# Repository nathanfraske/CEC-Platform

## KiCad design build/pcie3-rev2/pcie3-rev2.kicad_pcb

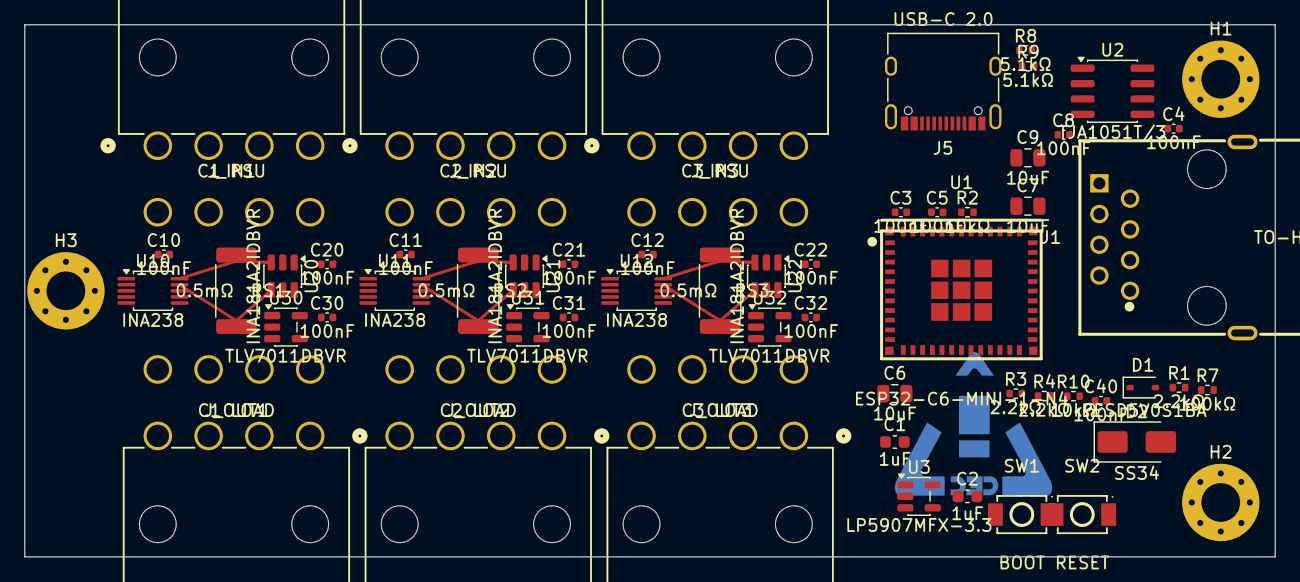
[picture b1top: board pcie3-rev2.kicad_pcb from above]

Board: 4 copper layers, 103.4 x 44.0 mm, 58 parts (1 on the bottom side), 32 nets.

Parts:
C1, C2: 1uF; C_0603_1608Metric
C3, C4, C5, C8, C10, C11, C12, C20, C21, C22, C30, C31, C32, C40: 100nF; C_0402_1005Metric
C6, C7, C9: 10uF; C_0805_2012Metric
D1: PESD5V0S1BA; D_SOD-323
D2: SS34; D_SMA
H1, H2, H3: MountingHole_3.2mm_M3_Pad_Via
J1: TO-HUB; RJ45_FTP_Shielded_Horizontal
J5: USB-C 2.0; USB_C_Receptacle_XKB_U262-16XN-4BVC11
J_IN1: C1 PSU; Molex_Mini-Fit_Jr_45586_2x04_P4.20mm_Horizontal
J_IN2: C2 PSU; Molex_Mini-Fit_Jr_45586_2x04_P4.20mm_Horizontal
J_IN3: C3 PSU; Molex_Mini-Fit_Jr_45586_2x04_P4.20mm_Horizontal
J_OUT1: C1 LOAD; Molex_Mini-Fit_Jr_45586_2x04_P4.20mm_Horizontal
J_OUT2: C2 LOAD; Molex_Mini-Fit_Jr_45586_2x04_P4.20mm_Horizontal
J_OUT3: C3 LOAD; Molex_Mini-Fit_Jr_45586_2x04_P4.20mm_Horizontal
LOGO1: CEC_Logo_Copper
R1, R3, R4: 2.2kΩ; R_0402_1005Metric
R2, R10: 10kΩ; R_0402_1005Metric
R7: 100kΩ; R_0402_1005Metric
R8, R9: 5.1kΩ; R_0402_1005Metric
RS1, RS2, RS3: 0.5mΩ; R_2512_6332Metric
SW1: BOOT; TS-1088-AR02016
SW2: RESET; TS-1088-AR02016
U1: ESP32-C6-MINI-1-N4; ESP32-C6-MINI-1
U2: TJA1051T/3; SOIC-8_3.9x4.9mm_P1.27mm
U3: LP5907MFX-3.3; SOT-23-5
U10, U11, U12: INA238; VSSOP-10_3x3mm_P0.5mm
U20, U21, U22: INA181A2IDBVR; SOT-23-6
U30, U31, U32: TLV7011DBVR; SOT-23-5

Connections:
+3V3: C2.1, C3.1, C7.1, C8.1, C10.1, C11.1, C12.1, C20.1, C21.1, C22.1, C30.1, C31.1, C32.1, R2.1, R3.2, R4.2, U1.3, U2.5, U3.5, U10.6, U11.2, U11.6, U12.1, U12.6, U20.6, U21.6, U22.6, U30.5, U31.5, U32.5
+5VSB: C1.1, C4.1, C6.1, D2.1, J1.1, U2.3, U3.1, U3.3
/CAN_H: J1.3, U2.7
/CAN_L: J1.6, U2.6
/CAN_RX: U1.27, U2.4
/CAN_TX: U1.26, U2.1
/DETAMPC1: U20.1, U30.3
/DETAMPC2: U21.1, U31.3
/DETAMPC3: U22.1, U32.3
/DETC1: U1.28, U30.1
/DETC2: U1.29, U31.1
/DETC3: U1.16, U32.1
/DETECT: D1.1, J1.8, R1.1, R7.1
/DETECT_SENSE: R7.2, U1.12
/EN: C5.1, R2.2, SW2.2, U1.8
/GPIO0: SW1.2, U1.23
/I2C_SCL: R4.1, U1.25, U10.5, U11.5, U12.5
/I2C_SDA: R3.1, U1.24, U10.4, U11.4, U12.4
/SENSEC1_HI: J_IN1.1, J_IN1.2, J_IN1.3, RS1.1, U10.10, U20.3
/SENSEC1_LO: J_OUT1.1, J_OUT1.2, J_OUT1.3, RS1.2, U10.8, U10.9, U20.4
/SENSEC2_HI: J_IN2.1, J_IN2.2, J_IN2.3, RS2.1, U11.10, U21.3
/SENSEC2_LO: J_OUT2.1, J_OUT2.2, J_OUT2.3, RS2.2, U11.8, U11.9, U21.4
/SENSEC3_HI: J_IN3.1, J_IN3.2, J_IN3.3, RS3.1, U12.10, U22.3
/SENSEC3_LO: J_OUT3.1, J_OUT3.2, J_OUT3.3, RS3.2, U12.8, U12.9, U22.4
/THRESH: C40.1, R10.2, U30.4, U31.4, U32.4
/THRESH_PWM: R10.1, U1.19
/USB_CC1: J5.A5, R8.1
/USB_CC2: J5.B5, R9.1
/USB_DM: J5.A7, J5.B7, U1.17
/USB_DP: J5.A6, J5.B6, U1.18
/VBUS: C9.1, D2.2, J5.A4, J5.A9, J5.B4, J5.B9
GND: C1.2, C2.2, C3.2, C4.2, C5.2, C6.2, C7.2, C8.2, C9.2, C10.2, C11.2, C12.2, C20.2, C21.2, C22.2, C30.2, C31.2, C32.2, C40.2, D1.2, H1.1, H2.1, H3.1, J1.2, J1.SH1, J1.SH2, J5.A1, J5.A12, J5.B1, J5.B12, J5.S1, J_IN1.4, J_IN1.5, J_IN1.6, J_IN1.7, J_IN1.8, J_IN2.4, J_IN2.5, J_IN2.6, J_IN2.7, J_IN2.8, J_IN3.4, J_IN3.5, J_IN3.6, J_IN3.7, J_IN3.8, J_OUT1.4, J_OUT1.5, J_OUT1.6, J_OUT1.7, J_OUT1.8, J_OUT2.4, J_OUT2.5, J_OUT2.6, J_OUT2.7, J_OUT2.8, J_OUT3.4, J_OUT3.5, J_OUT3.6, J_OUT3.7, J_OUT3.8, R1.2, R8.2, R9.2, SW1.1, SW2.1, U1.1, U1.2, U1.11, U1.14, U1.36, U1.37, U1.38, U1.39, U1.40, U1.41, U1.42, U1.43, U1.44, U1.45, U1.46, U1.47, U1.48, U1.49, U1.50, U1.51, U1.52, U1.53, U2.2, U2.8, U3.2, U10.1, U10.2, U10.7, U11.1, U11.7, U12.2, U12.7, U20.2, U20.5, U21.2, U21.5, U22.2, U22.5, U30.2, U31.2, U32.2

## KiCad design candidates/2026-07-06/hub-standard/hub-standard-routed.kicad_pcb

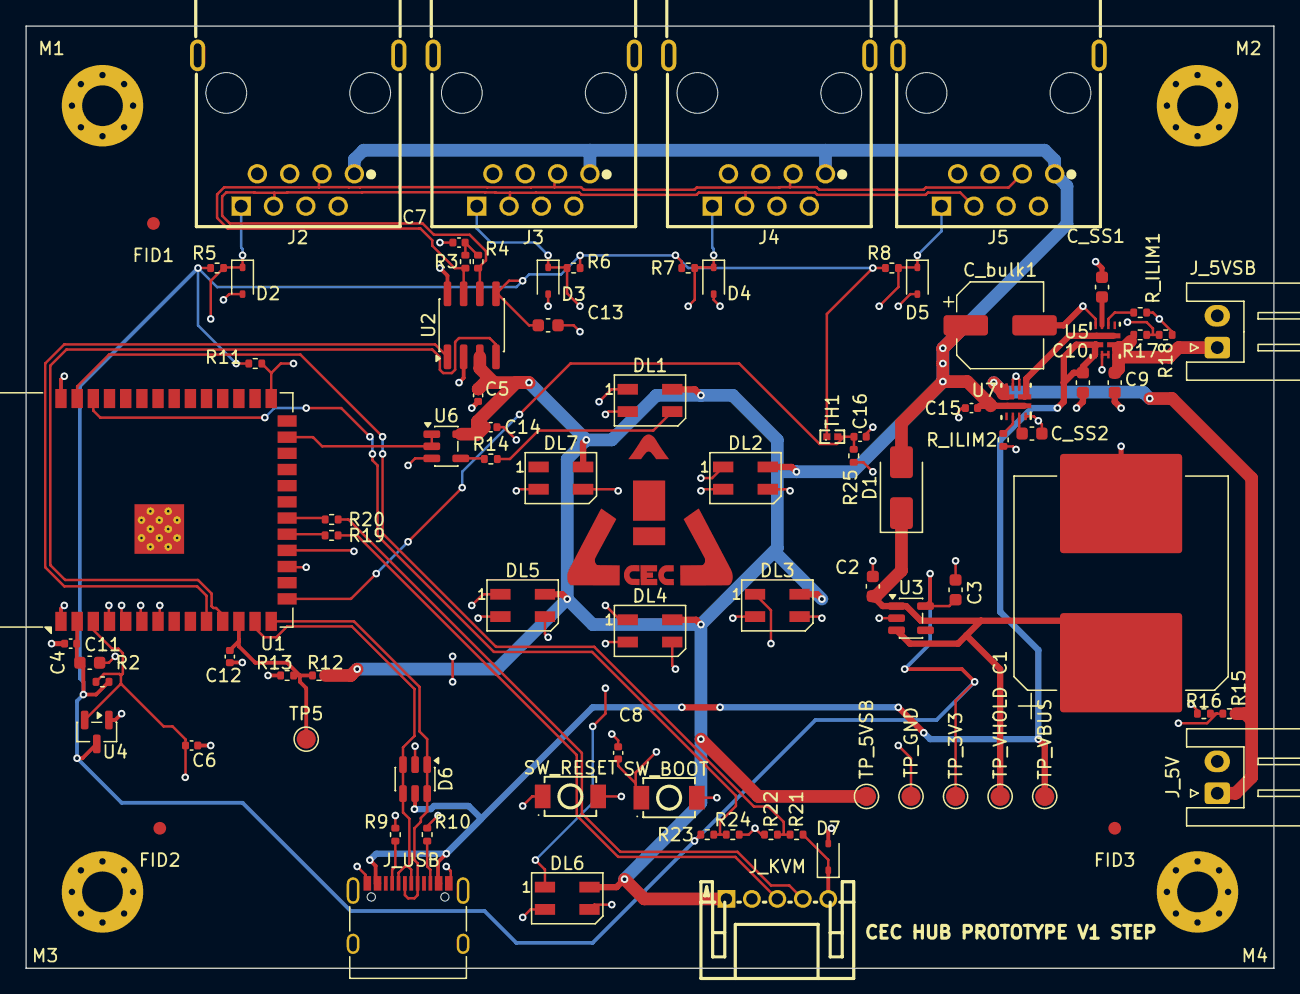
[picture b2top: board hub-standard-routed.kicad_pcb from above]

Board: 4 copper layers, 98.0 x 74.0 mm, 91 parts (0 on the bottom side), 47 nets.

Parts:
C1: 4700uF; CP_Elec_16x17.5
C2, C3, C9, C10: 1uF; C_0603_1608Metric
C4, C5, C6, C8, C14, C15, C16: 100nF; C_0402_1005Metric
C7: 4n7; C_0402_1005Metric
C11: 10uF; C_0603_1608Metric
C12: 10nF; C_0402_1005Metric
C13: 100nF; C_0603_1608Metric
C_SS1, C_SS2: 2.2uF; C_0603_1608Metric
C_bulk1: 470uF; CP_Elec_6.3x7.7
D1: SS14; D_SMA
D2, D3, D4, D5, D7: PESD5V0S1BA; D_SOD-323
D6: USBLC6-2SC6; SOT-23-6
DL1, DL2, DL3, DL4, DL5, DL6, DL7: SK6812MINI-E; LED_SK6812MINI_PLCC4_3.5x3.5mm_P1.75mm
FID1, FID2, FID3: Fiducial_1mm_Mask2mm
J2: PORT1; RJ45_FTP_Shielded_Horizontal
J3: PORT2; RJ45_FTP_Shielded_Horizontal
J4: PORT3; RJ45_FTP_Shielded_Horizontal
J5: PORT4; RJ45_FTP_Shielded_Horizontal
J_5V: MAIN_5V_IN; JST_XH_S2B-XH-A_1x02_P2.50mm_Horizontal
J_5VSB: 5VSB_IN; JST_XH_S2B-XH-A_1x02_P2.50mm_Horizontal
J_KVM: CEC_NANOKVM_AUX_5P; JST_PH_S5B-PH-K-S_1x05_P2.00mm_Horizontal
J_USB: USB-C; USB_C_Receptacle_XKB_U262-16XN-4BVC11
LOGO1: CEC_Logo_Copper
M1, M2, M3, M4: M3 Mount; MountingHole_3.2mm_M3_Pad_Via
R2, R5, R6, R7, R8, R11, R16, R18, R22, R24, R25: 10kΩ; R_0402_1005Metric
R3, R4: 60.4; R_0402_1005Metric
R9, R10: 5.1kΩ; R_0402_1005Metric
R12, R15, R17, R21, R23: 47kΩ; R_0402_1005Metric
R13: 27kΩ; R_0402_1005Metric
R14: 330Ω; R_0402_1005Metric
R19, R20: 33Ω; R_0402_1005Metric
R_ILIM1, R_ILIM2: 27kΩ; R_0402_1005Metric
SW_BOOT: SW_BOOT; TS-1088-AR02016
SW_RESET: SW_RST; TS-1088-AR02016
TH1: NTC 10k; NTC_0402_1005Metric
TP5: BLACKOUT; TestPoint_Pad_D1.5mm
TP_3V3: 3V3; TestPoint_Pad_D1.5mm
TP_5VSB: 5VSB; TestPoint_Pad_D1.5mm
TP_GND: GND; TestPoint_Pad_D1.5mm
TP_VBUS: USB_VBUS; TestPoint_Pad_D1.5mm
TP_VHOLD: 5V_HOLD; TestPoint_Pad_D1.5mm
U1: ESP32-S3-WROOM-1
U2: TJA1051T/3; SOIC-8_3.9x4.9mm_P1.27mm
U3: LP5907MFX-3.3; SOT-23-5
U4: TPS3839K33; SOT-23
U5, U7: TPS2121RUXR; RUX0012A
U6: SN74AHCT1G08; SOT-23-5

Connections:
+3V3: C3.1, C4.1, C11.1, C13.1, R2.1, R5.1, R6.1, R7.1, R8.1, R11.1, R23.1, TH1.1, TP_3V3.1, U1.2 (3V3), U2.5 (VIO), U3.5 (OUT), U4.3 (VDD)
+5VSB: C5.1, C14.1, C15.1, C_bulk1.1, D1.2 (A), DL1.4 (VDD), DL2.4 (VDD), DL3.4 (VDD), DL4.4 (VDD), DL5.4 (VDD), DL6.4 (VDD), DL7.4 (VDD), J2.1 (VCC), J3.1 (VCC), J4.1 (VCC), J5.1 (VCC), J_KVM.1 (+5VSB), R12.1, TP_5VSB.1, U2.3 (VCC), U6.5 (VCC), U7.1 (OUT), U7.8 (OUT)
/5VSB_RAW: C9.1, J_5VSB.1 (VCC), R17.1, U5.6 (PR1), U5.7 (IN1)
/5VSB_SENSE: R17.2, R18.1, U1.18 (IO10)
/+5V_HOLD: C1.1, C2.1, D1.1 (K), TP_VHOLD.1, U3.1 (IN), U3.3 (EN)
/AUX_RXC: J_KVM.4 (UART_RX), R20.2
/AUX_TXC: J_KVM.3 (UART_TX), R19.2
/AUX_UART_RX: R20.1, U1.20 (IO12)
/AUX_UART_TX: R19.1, U1.19 (IO11)
/BLACKOUT_SENSE: C12.1, R12.2, R13.1, TP5.1, U1.12 (IO8)
/CAN_H: J2.3 (CAN1_H), J3.3 (CAN1_H), J4.3 (CAN1_H), J5.3 (CAN1_H), R3.1, U2.7 (CANH)
/CAN_L: J2.6 (CAN1_L), J3.6 (CAN1_L), J4.6 (CAN1_L), J5.6 (CAN1_L), R4.2, U2.6 (CANL)
/CAN_MID: C7.1, R3.2, R4.1
/CAN_RX: U1.11 (IO18), U2.4 (RXD)
/CAN_TX: U1.10 (IO17), U2.1 (TXD)
/DETECT1: D2.1 (K), J2.8 (DETECT), R5.2, U1.4 (IO4)
/DETECT2: D3.1 (K), J3.8 (DETECT), R6.2, U1.5 (IO5)
/DETECT3: D4.1 (K), J4.8 (DETECT), R7.2, U1.6 (IO6)
/DETECT4: D5.1 (K), J5.8 (DETECT), R8.2, U1.7 (IO7)
/EN: C6.2, R2.2, SW_RESET.2, U1.3 (EN), U4.2 (~RESET)
/GPIO0: C8.1, R11.2, SW_BOOT.2, U1.27 (IO0)
/HUB_3V3_SENSE: R23.2, R24.1, U1.38 (IO2)
/KVM_3V3_REF: D7.1 (K), J_KVM.5 (KVM_3V3), R21.1
/KVM_3V3_SENSE: R21.2, R22.1, U1.39 (IO1)
/LED_DATA: U1.25 (IO48), U6.1 (A), U6.2 (B)
/LED_DATA_BUF: R14.1, U6.4 (Y)
/LED_DATA_DIN: DL1.3 (DIN), R14.2
/MAIN_5V_RAW: J_5V.1 (VCC), R15.1, U7.6 (PR1), U7.7 (IN1)
/MAIN_5V_SENSE: R15.2, R16.1, U1.17 (IO9)
/PSU_5V: U5.1 (OUT), U5.8 (OUT), U7.2 (IN2), U7.3 (CP2)
/TEMP_HUB: C16.1, R25.1, TH1.2, U1.15 (IO3)
/U7_ILM: R_ILIM2.1, U7.10 (ILM)
/U7_SS: C_SS2.1, U7.11 (SS)
/USB_CC1: J_USB.A5 (CC1), R9.1
/USB_CC2: J_USB.B5 (CC2), R10.1
/USB_DM: D6.3 (I/O2), D6.4 (I/O2), J_USB.A7 (D-), J_USB.B7 (D-), U1.13 (USB_D-)
/USB_DP: D6.1 (I/O1), D6.6 (I/O1), J_USB.A6 (D+), J_USB.B6 (D+), U1.14 (USB_D+)
/USB_VBUS: C10.1, D6.5 (VBUS), J_USB.A4 (VBUS), J_USB.A9 (VBUS), J_USB.B4 (VBUS), J_USB.B9 (VBUS), TP_VBUS.1, U5.2 (IN2), U5.3 (CP2)
GND: C1.2, C2.2, C3.2, C4.2, C5.2, C6.1, C7.2, C8.2, C9.2, C10.2, C11.2, C12.2, C13.2, C14.2, C15.2, C16.2, C_SS1.1, C_SS2.2, C_bulk1.2, D2.2 (A), D3.2 (A), D4.2 (A), D5.2 (A), D6.2 (GND), D7.2 (A), DL1.2 (VSS), DL2.2 (VSS), DL3.2 (VSS), DL4.2 (VSS), DL5.2 (VSS), DL6.2 (VSS), DL7.2 (VSS), J2.2 (GND), J2.SH1 (SHIELD), J2.SH2 (SHIELD), J3.2 (GND), J3.SH1 (SHIELD), J3.SH2 (SHIELD), J4.2 (GND), J4.SH1 (SHIELD), J4.SH2 (SHIELD), J5.2 (GND), J5.SH1 (SHIELD), J5.SH2 (SHIELD), J_5V.2 (GND), J_5VSB.2 (GND), J_KVM.2 (GND), J_USB.A1 (GND), J_USB.A12 (GND), J_USB.B1 (GND), J_USB.B12 (GND), J_USB.S1 (SHIELD), M1.1, M2.1, M3.1, M4.1, R9.2, R10.2, R13.2, R16.2, R18.2, R22.2, R24.2, R25.2, R_ILIM1.2, R_ILIM2.2, SW_BOOT.1, SW_RESET.1, TP_GND.1, U1.1 (GND), U1.40 (GND), U1.41 (GND), U2.2 (GND), U2.8 (S), U3.2 (GND), U4.1 (GND), U5.4 (OV2), U5.5 (OV1), U5.12 (GND), U6.3 (GND), U7.4 (OV2), U7.5 (OV1), U7.12 (GND)
unnamed: DL1.1 (DOUT), DL2.3 (DIN)
unnamed: DL2.1 (DOUT), DL3.3 (DIN)
unnamed: DL3.1 (DOUT), DL4.3 (DIN)
unnamed: DL4.1 (DOUT), DL5.3 (DIN)
unnamed: DL5.1 (DOUT), DL6.3 (DIN)
unnamed: DL6.1 (DOUT), DL7.3 (DIN)
unnamed: R_ILIM1.1, U5.10 (ILM)
unnamed: C_SS1.2, U5.11 (SS)

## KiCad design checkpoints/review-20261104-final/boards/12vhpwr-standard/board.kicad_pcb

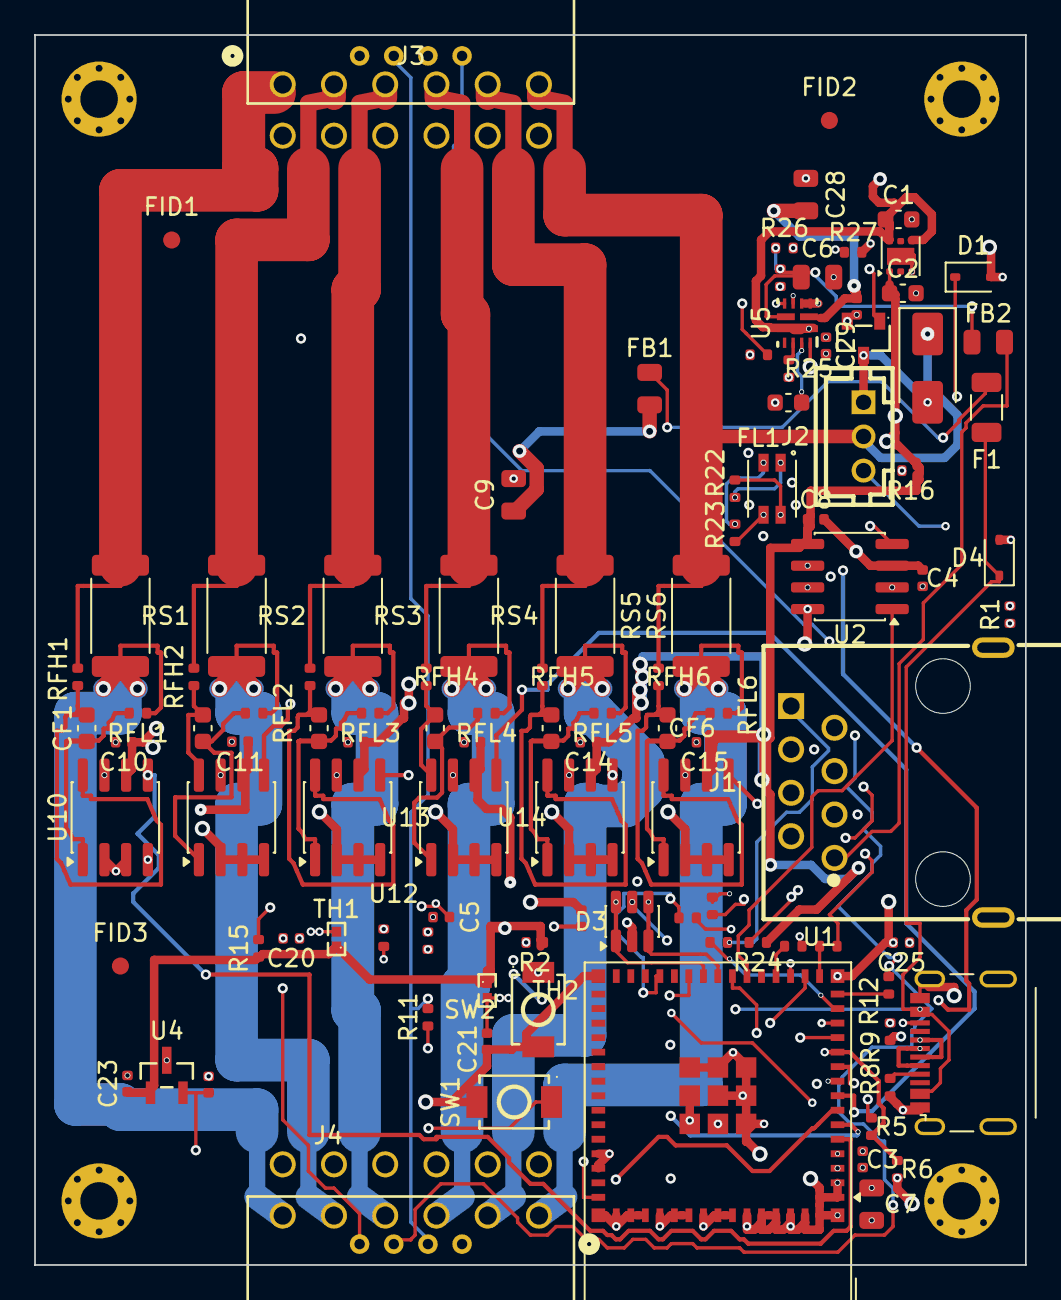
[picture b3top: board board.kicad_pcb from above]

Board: 6 copper layers, 58.0 x 72.0 mm, 110 parts (0 on the bottom side), 73 nets.

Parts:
C1: 10uF; C_0603_1608Metric
C2: 1uF; C_0603_1608Metric
C3, C4, C5, C8, C10, C11, C12, C13, C14, C15, C20, C21, C22, C23, C25, C27, C29: 100nF; C_0402_1005Metric
C6, C7, C9, C28: 10uF; C_0805_2012Metric
C24: 1nF; C_0402_1005Metric
C26: 2.2uF; C_0603_1608Metric
CF1, CF2, CF3, CF4, CF5, CF6: 470nF; C_0603_1608Metric
D1, D4: PESD5V0S1BA; D_SOD-323
D3: USBLC6-2SC6; SOT-23-6
D5: SS34; D_SMA
F1: 750mA/16V PTC; R_1206_3216Metric
FB1: MPZ2012S601AT000; C_0805_2012Metric
FB2: 0R; C_0805_2012Metric
FID1, FID2, FID3: Fiducial_1mm_Mask2mm
FL1: ACT1210L-101-2P-TL00 (DNP); TDK_ACT1210L_CEC_13_24
H1, H2, H3, H4: M2_PTH_GND_Slim_6mm_Hardware; MountingHole_2.2mm_M2_Pad_Via_Slim_6mm_Hardware
J1: TO-HUB; RJ45_FTP_Shielded_Horizontal
J2: CEC_FAN_3P; JST_PH_B3B-PH-K-S_1x03_P2.00mm_Vertical
J3: 12V-2x6 IN; CEC_12V2x6_Horizontal
J4: 12V-2x6 OUT pigtail; CEC_12V2x6_Horizontal
J5: USB-C 2.0; USB_C_Receptacle_GCT_USB4215-03-A
Q1: AO3400A; SOT-23-3_L2.9-W1.3-P1.90-LS2.4-BR
R1: 2.2kΩ; R_0402_1005Metric
R2, R6, R15, R16, R20, R21, R24, R27: 10kΩ; R_0402_1005Metric
R5: 47kΩ; R_0402_1005Metric
R7, R25, R28: 100kΩ; R_0402_1005Metric
R8, R9: 5.1kΩ; R_0402_1005Metric
R10, R11, R12, R13, R17: 1kΩ; R_0402_1005Metric
R14: 100Ω; R_0402_1005Metric
R22, R23: 0Ω; R_0402_1005Metric
R26: 43.2kΩ; R_0402_1005Metric
R29: 33kΩ; R_0402_1005Metric
RFH1, RFH2, RFH3, RFH4, RFH5, RFH6: 10Ω; R_0402_1005Metric
RFL1, RFL2, RFL3, RFL4, RFL5, RFL6: 10Ω; R_0402_1005Metric
RS1, RS2, RS3, RS4, RS5, RS6: 1mΩ; R_2512_6332Metric
SW1: BOOT; TS-1088-AR02016
SW2: RESET; TS-1088-AR02016
TH1, TH2: NTC 10k; NTC_0402_1005Metric
U1: ESP32-S3-MINI-1-N4R2; ESP32-S2-MINI-1_NoAntKeepout
U2: TJA1051T/3; SOIC-8_3.9x4.9mm_P1.27mm
U4: REF3030; REF3030_DBZ3
U5: TPS2121RUXR; RUX0012A
U10, U11, U12, U13, U14, U15: INA240A3; SOIC-8_3.9x4.9mm_P1.27mm
U16: TLV75533PDRVR; WSON-6-1EP_2x2mm_P0.65mm_EP1x1.6mm

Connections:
+3V3: C2.1, C3.1, C7.1, C8.1, C10.1, C11.1, C12.1, C13.1, C14.1, C15.1, C23.1, R2.1, R15.1, R16.1, R24.1, TH1.1, TH2.1, U1.3, U2.5, U4.1, U10.6, U11.6, U12.6, U13.6, U14.6, U15.6, U16.1
+5VSB: C1.1, C4.1, C8.2, C29.1, U2.3, U5.1, U5.8, U16.4, U16.6
/01-input/FAN_GATE: Q1.1, R14.2, R15.2
/01-input/FAN_RET: D5.2, J2.1, Q1.3
/01-input/FAN_TACH: J2.3, R16.2, R17.1
/08-usb/U5_ILM: R25.1, U5.10
/08-usb/U5_OV1: R26.2, R27.1, U5.5
/08-usb/U5_PR1: R28.2, R29.1, U5.6
/08-usb/U5_SS: C26.1, U5.11
/CAN_H: FL1.1, J1.3, R22.1
/CAN_H_INT: FL1.3, R22.2, U2.7
/CAN_L: FL1.2, J1.6, R23.1
/CAN_L_INT: FL1.4, R23.2, U2.6
/CAN_RX: U1.22, U2.4
/CAN_TX: U1.21, U2.1
/DETECT: D1.1, J1.8, R1.1, R7.1
/DETECT_SENSE: R7.2, U1.14
/EN: C5.1, R2.2, SW2.2, U1.45
/FAN_12V: D5.1, J2.2, J3.6, R5.1, RFH6.1, RS6.1
/FAN_EN: R14.1, U1.25
/FAN_TACH_GPIO: R17.2, U1.27
/GPIO0: C25.1, R24.2, SW1.2, U1.4
/IN1_N: CF1.2, RFL1.2, U10.1
/IN1_P: CF1.1, RFH1.2, U10.8
/IN2_N: CF2.2, RFL2.2, U11.1
/IN2_P: CF2.1, RFH2.2, U11.8
/IN3_N: CF3.2, RFL3.2, U12.1
/IN3_P: CF3.1, RFH3.2, U12.8
/IN4_N: CF4.2, RFL4.2, U13.1
/IN4_P: CF4.1, RFH4.2, U13.8
/IN5_N: CF5.2, RFL5.2, U14.1
/IN5_P: CF5.1, RFH5.2, U14.8
/IN6_N: CF6.2, RFL6.2, U15.1
/IN6_P: CF6.1, RFH6.2, U15.8
/ISENSEP1: U1.5, U10.5
/ISENSEP2: U1.6, U11.5
/ISENSEP3: U1.7, U12.5
/ISENSEP4: U1.8, U13.5
/ISENSEP5: U1.9, U14.5
/ISENSEP6: U1.10, U15.5
/SB_CBL_PRES: J3.16, J4.16, R13.1
/SB_CBL_PRES_GPIO: R13.2, U1.16
/SB_PWR_STABLE: J3.15, J4.15, R12.1
/SB_PWR_STABLE_GPIO: R12.2, U1.15
/SB_SENSE0: J3.13, J4.13, R10.1
/SB_SENSE0_GPIO: R10.2, U1.19
/SB_SENSE1: J3.14, J4.14, R11.1
/SB_SENSE1_GPIO: R11.2, U1.13
/SENSEP1_HI: J3.1, RFH1.1, RS1.1
/SENSEP1_LO: J4.6, RFL1.1, RS1.2
/SENSEP2_HI: J3.2, RFH2.1, RS2.1
/SENSEP2_LO: J4.5, RFL2.1, RS2.2
/SENSEP3_HI: J3.3, RFH3.1, RS3.1
/SENSEP3_LO: J4.4, RFL3.1, RS3.2
/SENSEP4_HI: J3.4, RFH4.1, RS4.1
/SENSEP4_LO: J4.3, RFL4.1, RS4.2
/SENSEP5_HI: J3.5, RFH5.1, RS5.1
/SENSEP5_LO: J4.2, RFL5.1, RS5.2
/SENSEP6_LO: J4.1, RFL6.1, RS6.2
/TEMP1: C20.1, R20.1, TH1.2, U1.17
/TEMP2: C21.1, R21.1, TH2.2, U1.18
/USB_CC1: J5.A5, R8.1
/USB_CC2: J5.B5, R9.1
/USB_DM: D3.3, D3.4, J5.A7, J5.B7, U1.23
/USB_DP: D3.1, D3.6, J5.A6, J5.B6, U1.24
/VBUS: C9.1, C27.1, C28.1, FB1.2, U5.2
/VBUS_F: F1.2, FB1.1
/VBUS_RAW: D3.5, D4.1, F1.1, J5.A4, J5.A9, J5.B4, J5.B9
/VCC_RAW: FB2.2, J1.1
/VCC_RJ45: C6.1, FB2.1, R26.1, R28.1, U5.7
/VRAIL_DIV: C24.1, R5.2, R6.1, U1.11
/VREF: C22.1, U1.12, U4.2
GND: C1.2, C2.2, C3.2, C4.2, C5.2, C6.2, C7.2, C9.2, C10.2, C11.2, C12.2, C13.2, C14.2, C15.2, C20.2, C21.2, C22.2, C23.2, C24.2, C25.2, C26.2, C27.2, C28.2, C29.2, D1.2, D3.2, D4.2, H1.1, H2.1, H3.1, H4.1, J1.2, J1.SH1, J1.SH2, J3.7, J3.8, J3.9, J3.10, J3.11, J3.12, J4.7, J4.8, J4.9, J4.10, J4.11, J4.12, J5.A1, J5.A12, J5.B1, J5.B12, J5.S1, Q1.2, R1.2, R6.2, R8.2, R9.2, R20.2, R21.2, R25.2, R27.2, R29.2, SW1.1, SW2.1, U1.1, U1.2, U1.42, U1.43, U1.46, U1.47, U1.48, U1.49, U1.50, U1.51, U1.52, U1.53, U1.54, U1.55, U1.56, U1.57, U1.58, U1.59, U1.60, U1.61, U1.62, U1.63, U1.64, U1.65, U2.2, U2.8, U4.3, U5.3, U5.4, U5.12, U10.2, U10.3, U10.4, U10.7, U11.2, U11.3, U11.4, U11.7, U12.2, U12.3, U12.4, U12.7, U13.2, U13.3, U13.4, U13.7, U14.2, U14.3, U14.4, U14.7, U15.2, U15.3, U15.4, U15.7, U16.3, U16.7
